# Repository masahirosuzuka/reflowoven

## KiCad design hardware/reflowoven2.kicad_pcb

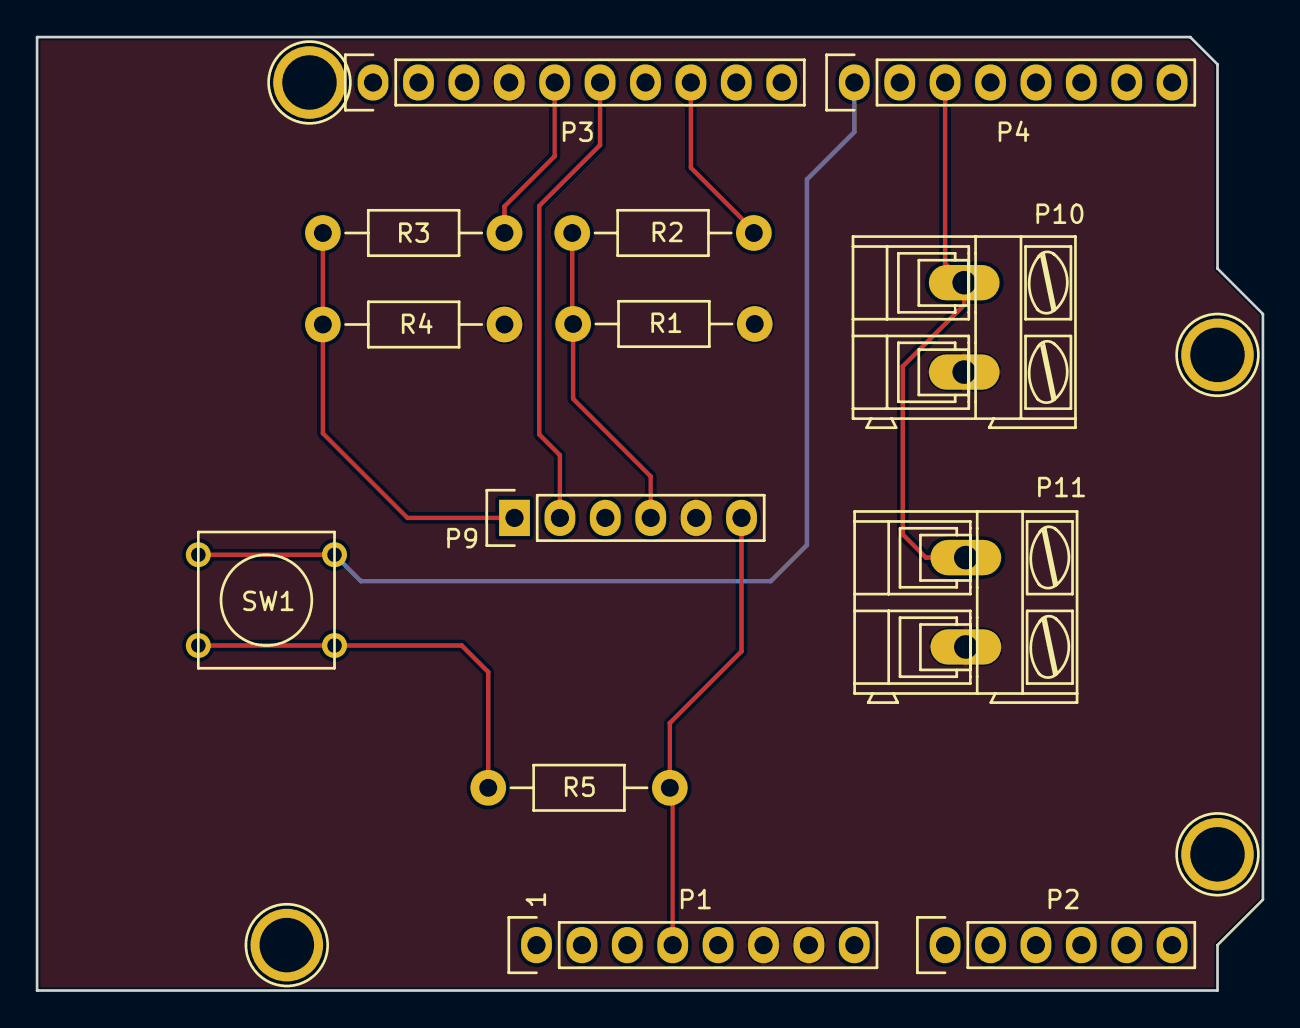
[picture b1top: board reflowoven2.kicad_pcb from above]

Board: 2 copper layers, 68.6 x 53.3 mm, 17 parts (0 on the bottom side), 12 nets.

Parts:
P1: Power; Socket_Strip_Arduino_1x08
P2: Analog; Socket_Strip_Arduino_1x06
P3: Digital; Socket_Strip_Arduino_1x10
P4: Digital; Socket_Strip_Arduino_1x08
P5, P6, P7, P8: CONN_1; Arduino_1pin
P9: type K thermocouple; Socket_Strip_Straight_1x06
P10, P11: SSR; AK300-2
R1, R3: 4.7K; Resistor_Horizontal_RM10mm
R2, R4: 2.2K; Resistor_Horizontal_RM10mm
R5: 330; Resistor_Horizontal_RM10mm
SW1: SW_PUSH; SW_PUSH_SMALL

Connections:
+3.3V: P1.4, P9.6, R5.1
/A4(SDA): P2.5, P3.2
/A5(SCL): P2.6, P3.1
/MISO: P3.6, P9.2
/SCK: P3.5, R3.1
/SS: P3.8, R1.1
/SSR: P4.3, P10.1, P11.1
/START_STOP: P4.1, SW1.1
GND: P1.6, P1.7, P3.4, P9.5, P10.2, P11.2, R2.2, R4.2
unnamed: P9.1, R3.2, R4.1
unnamed: P9.4, R1.2, R2.1
unnamed: R5.2, SW1.2

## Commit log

2015-09-09 fix value miss
2015-11-23 add arduino.h
2015-12-01 Re-design hardware
